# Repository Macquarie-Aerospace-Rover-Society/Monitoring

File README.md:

# Monitoring
The monitoring and GPIO cards will all be under this repo.

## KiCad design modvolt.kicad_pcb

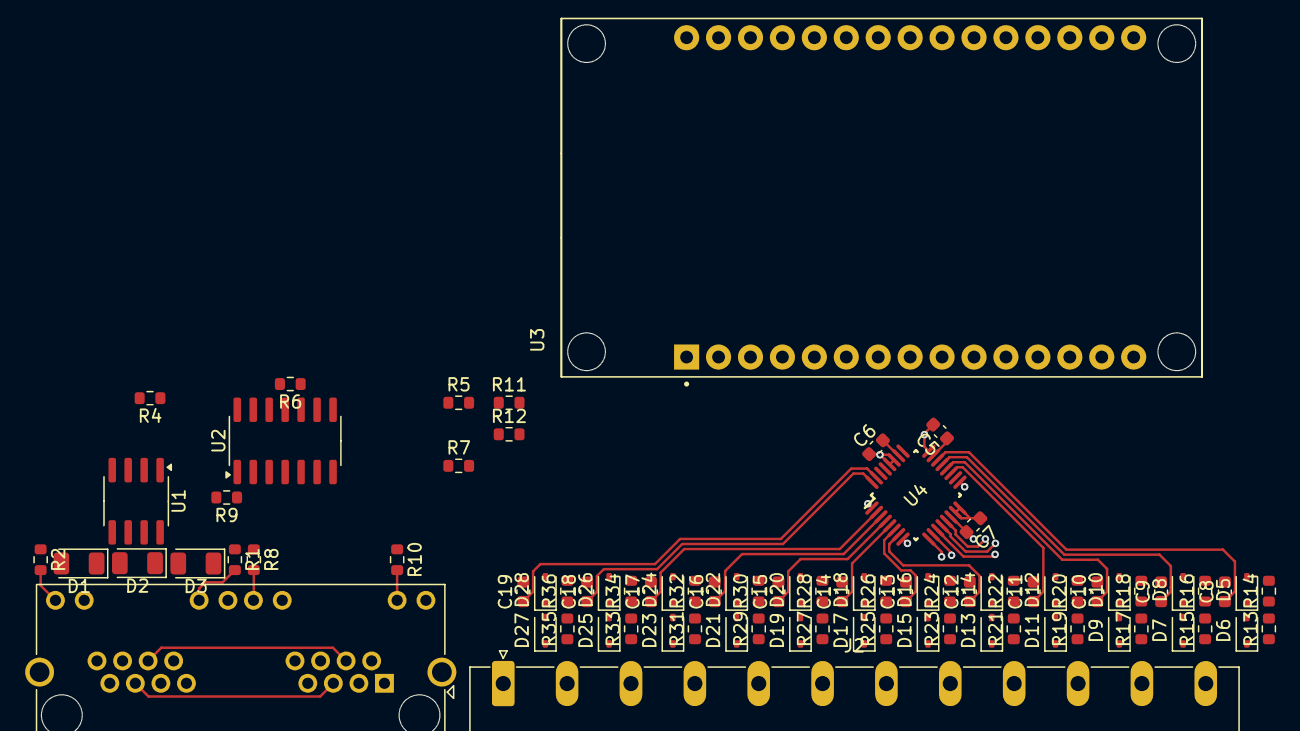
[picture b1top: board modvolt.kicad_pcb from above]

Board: 2 copper layers, 83 parts (0 on the bottom side), 52 nets.

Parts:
C5: 1u; C_0603_1608Metric
C6, C7, C8, C9, C10, C11, C12, C13, C14, C15, C16, C17, C18, C19: 100n; C_0603_1608Metric
D1, D3: D_TVS; D_1206_3216Metric
D2: Diode_SMD:D_1206_3216Metric; D_1206_3216Metric
D5, D6, D7, D8, D9, D10, D11, D12, D13, D14, D15, D16, D17, D18, D19, D20, D21, D22, D23, D24, D25, D26, D27, D28: 1N4148; D_SOD-323
J1: 8P8C_LED_Shielded_x2; RJ45_Amphenol_RJHSE538X-02
J2: Conn_01x13_Socket; PhoenixContact_MC_1,5_12-G-5.08_1x12_P5.08mm_Horizontal
R1, R8, R10: 470R; R_0603_1608Metric
R2: 330R; R_0603_1608Metric
R4, R5, R7, R9, R12, R13, R14, R15, R16, R17, R18, R19, R20, R21, R22, R23, R24, R25, R26, R27, R28, R29, R30, R31, R32, R33, R34, R35, R36: 4K7; R_0603_1608Metric
R6: 56K; R_0603_1608Metric
R11: 2K4; R_0603_1608Metric
U1: MAX485E; SOIC-8_3.9x4.9mm_P1.27mm
U2: 74HC14; SOIC-14_3.9x8.7mm_P1.27mm
U3: ESP32-DEVKIT-V1; MODULE_ESP32_DEVKIT_V1
U4: ADS114S08BIPBSR; PBS0032A_N

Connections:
+3.3V: D6.1 (K), D7.1 (K), D9.1 (K), D11.1 (K), D13.1 (K), D15.1 (K), D17.1 (K), D19.1 (K), D21.1 (K), D23.1 (K), D25.1 (K), D27.1 (K), J1.1, J1.2, J1.13, J1.14, R2.1, R9.2, U3.1 (3V3), U3.16 (EN)
+5V: J1.7, J1.8, J1.19, J1.20, R1.1, R4.1, R7.1, U1.8 (VCC), U2.14 (VCC)
A1: J2.2, R35.1
A2: J2.3, R33.1
A3: J2.4, R31.1
A4: J2.5, R29.1
A5: J2.6, R27.1
A6: J2.7, R25.1
A7: J2.8, R23.1
A8: J2.9, R21.1
A9: J2.10, R19.1
A10: J2.11, R17.1
A11: J2.12, R15.1
CH1: C19.1, D27.2 (A), D28.1 (K), R35.2, R36.1, U4.31 (REFN1_AIN7)
CH2: C18.1, D25.2 (A), D26.1 (K), R33.2, R34.1, U4.32 (REFP1_AIN6)
CH3: C17.1, D23.2 (A), D24.1 (K), R31.2, R32.1, U4.2 (AIN5)
CH4: C16.1, D21.2 (A), D22.1 (K), R29.2, R30.1, U4.3 (AIN4)
CH5: C15.1, D19.2 (A), D20.1 (K), R27.2, R28.1, U4.4 (AIN3)
CH6: C14.1, D17.2 (A), D18.1 (K), R25.2, R26.1, U4.5 (AIN2)
CH7: C13.1, D15.2 (A), D16.1 (K), R23.2, R24.1, U4.6 (AIN1)
CH8: C12.1, D13.2 (A), D14.1 (K), R21.2, R22.1, U4.7 (AIN0)
CH9: C11.1, D11.2 (A), D12.1 (K), R19.2, R20.1, U4.19 (GPIO3_AIN11)
CH10: C10.1, D9.2 (A), D10.1 (K), R17.2, R18.1, U4.20 (GPIO2_AIN10)
CH11: C9.1, D7.2 (A), D8.1 (K), R15.2, R16.1, U4.21 (GPIO1_AIN9)
CH12: C8.1, D5.1 (K), D6.2 (A), R13.2, R14.1, U4.22 (GPIO0_AIN8)
CS: U3.8 (D5), U4.9 (CS_N)
INT: U3.14 (D22), U4.13 (DRDY_N)
MISO: U3.10 (D19), U4.12 (DOUT_DRDY_N)
MOSI: U3.15 (D23), U4.10 (DIN)
unnamed: D1.1 (A1), D2.2 (A2), J1.4, J1.16, R4.2, U1.6 (A)
unnamed: D1.2 (A2), D3.1 (A1), J1.3, J1.6, J1.15, J1.18
unnamed: D2.1 (A1), D3.2 (A2), J1.5, J1.17, R5.1, U1.7 (B)
unnamed: R6.2, U2.13
unnamed: R6.1, U1.4 (DI), U2.10
unnamed: J1.22, R1.2
unnamed: J1.24, R2.2
unnamed: R8.1, U2.2, U2.11
unnamed: R10.1, U2.6
unnamed: R11.2, U2.4, U2.5
unnamed: U1.2 (~RE), U1.3 (DE), U2.12
unnamed: R7.2, U1.1 (RO), U2.9
unnamed: U2.3, U2.8
unnamed: C6.1, U4.26 (AVDD)
unnamed: C7.1, U4.15 (IOVDD), U4.16 (DVDD)
unnamed: C5.1, U4.23 (REFOUT)
OK: C5.2, C6.2, C7.2, C8.2, C9.2, C10.2, C11.2, C12.2, C13.2, C14.2, C15.2, C16.2, C17.2, C18.2, C19.2, D5.2 (A), D8.2 (A), D10.2 (A), D12.2 (A), D14.2 (A), D16.2 (A), D18.2 (A), D20.2 (A), D22.2 (A), D24.2 (A), D26.2 (A), D28.2 (A), J1.9, J1.11, J1.21, J1.23, J1.SH, J2.1, R5.2, R12.1, R14.2, R16.2, R18.2, R20.2, R22.2, R24.2, R26.2, R28.2, R30.2, R32.2, R34.2, R36.2, U1.5 (GND), U2.7 (GND), U3.2 (GND), U3.29 (GND__1), U4.1 (AINCOM), U4.8 (START_SYNC), U4.14 (DGND), U4.17 (CLK), U4.24 (REFCOM), U4.27 (AVSS), U4.28 (AVSS)
RX: R9.1, U2.1, U3.6 (RX2)
RXLED: J1.12, R8.2
SCK: U3.9 (D18), U4.11 (SCLK)
TX: R11.1, R12.2, U3.7 (TX2)
TXLED: J1.10, R10.2
nRST: U3.23 (D25), U4.18 (RESET_N)

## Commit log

2025-01-25 Mostly sorted schematic
    No board
2025-01-25 RS485 test spaghetti
    Yep... It's most certainly code. You may be wondering how one writes such dogshit but here we are
2025-02-07 I am ashamed
    I have been coerced into uploading this abomination. If it were up to me, this would never have seen the light of day
2025-02-09 Update
    Begun SPI integration, lost the will to live.
